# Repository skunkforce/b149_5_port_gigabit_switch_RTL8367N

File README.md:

# edgy_board number b149
This design is part of the [edgy board project](https://github.com/skunkforce/edgy_boards). It provides the functionality of chip XXXX via interfaces YYYY. 

# getting started
This repository uses submodules. After cloning use the command 

```$ git submodule update --init --recursive```

to pull the submodules before opening the project with kicad. 

# Tests
Tests can be found in [TESTS.md](TESTS.md)

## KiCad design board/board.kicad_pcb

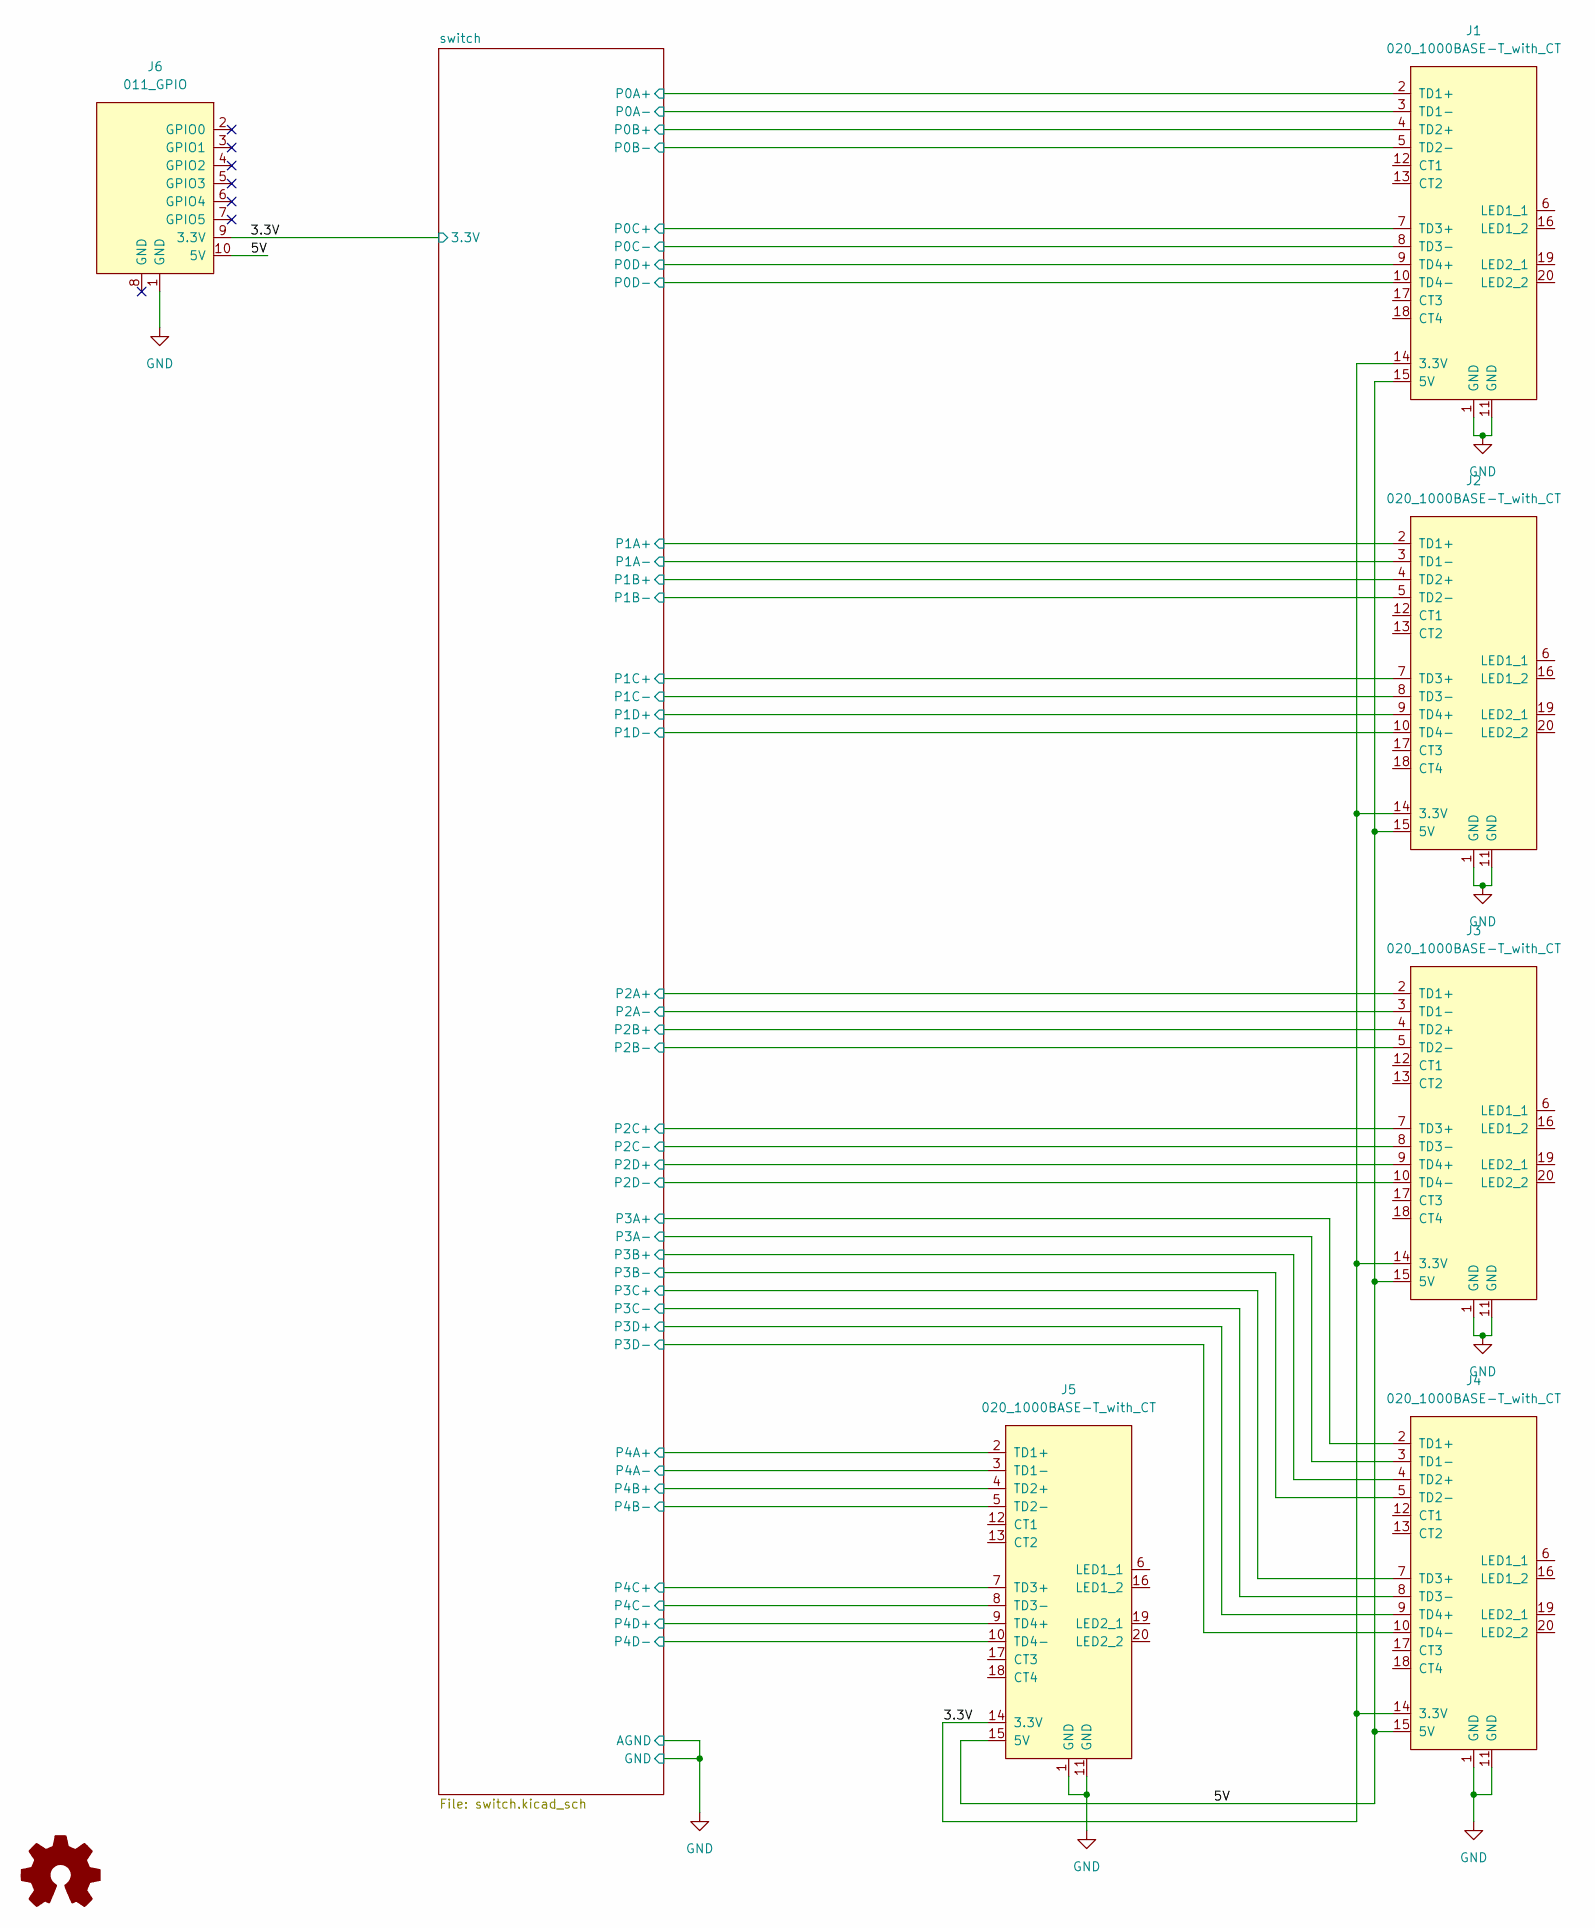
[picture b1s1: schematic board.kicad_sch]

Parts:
J1, J2, J3, J4, J5: 020_1000BASE-T_with_CT; on_edge_2x10_host
J6: 011_GPIO; on_edge_2x05_device
LOGO1: Logo_Open_Hardware_Small; OSHW-Symbol_6.7x6mm_SilkScreen

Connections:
/3.3V: J1.14 (3.3V), J2.14 (3.3V), J3.14 (3.3V), J4.14 (3.3V), J5.14 (3.3V), J6.9 (3.3V); also elsewhere on the board
/5V: J1.15 (5V), J2.15 (5V), J3.15 (5V), J4.15 (5V), J5.15 (5V), J6.10 (5V)
/switch/P0A+: J1.2 (TD1+); also elsewhere on the board
/switch/P0A-: J1.3 (TD1-); also elsewhere on the board
/switch/P0B+: J1.4 (TD2+); also elsewhere on the board
/switch/P0B-: J1.5 (TD2-); also elsewhere on the board
/switch/P0C+: J1.7 (TD3+); also elsewhere on the board
/switch/P0C-: J1.8 (TD3-); also elsewhere on the board
/switch/P0D+: J1.9 (TD4+); also elsewhere on the board
/switch/P0D-: J1.10 (TD4-); also elsewhere on the board
/switch/P1A+: J2.2 (TD1+); also elsewhere on the board
/switch/P1A-: J2.3 (TD1-); also elsewhere on the board
/switch/P1B+: J2.4 (TD2+); also elsewhere on the board
/switch/P1B-: J2.5 (TD2-); also elsewhere on the board
/switch/P1C+: J2.7 (TD3+); also elsewhere on the board
/switch/P1C-: J2.8 (TD3-); also elsewhere on the board
/switch/P1D+: J2.9 (TD4+); also elsewhere on the board
/switch/P1D-: J2.10 (TD4-); also elsewhere on the board
/switch/P2A+: J3.2 (TD1+); also elsewhere on the board
/switch/P2A-: J3.3 (TD1-); also elsewhere on the board
/switch/P2B+: J3.4 (TD2+); also elsewhere on the board
/switch/P2B-: J3.5 (TD2-); also elsewhere on the board
/switch/P2C+: J3.7 (TD3+); also elsewhere on the board
/switch/P2C-: J3.8 (TD3-); also elsewhere on the board
/switch/P2D+: J3.9 (TD4+); also elsewhere on the board
/switch/P2D-: J3.10 (TD4-); also elsewhere on the board
/switch/P3A+: J4.2 (TD1+); also elsewhere on the board
/switch/P3A-: J4.3 (TD1-); also elsewhere on the board
/switch/P3B+: J4.4 (TD2+); also elsewhere on the board
/switch/P3B-: J4.5 (TD2-); also elsewhere on the board
/switch/P3C+: J4.7 (TD3+); also elsewhere on the board
/switch/P3C-: J4.8 (TD3-); also elsewhere on the board
/switch/P3D+: J4.9 (TD4+); also elsewhere on the board
/switch/P3D-: J4.10 (TD4-); also elsewhere on the board
/switch/P4A+: J5.2 (TD1+); also elsewhere on the board
/switch/P4A-: J5.3 (TD1-); also elsewhere on the board
/switch/P4B+: J5.4 (TD2+); also elsewhere on the board
/switch/P4B-: J5.5 (TD2-); also elsewhere on the board
/switch/P4C+: J5.7 (TD3+); also elsewhere on the board
/switch/P4C-: J5.8 (TD3-); also elsewhere on the board
/switch/P4D+: J5.9 (TD4+); also elsewhere on the board
/switch/P4D-: J5.10 (TD4-); also elsewhere on the board
GND: J1.1 (GND), J1.11 (GND), J2.1 (GND), J2.11 (GND), J3.1 (GND), J3.11 (GND), J4.1 (GND), J4.11 (GND), J5.1 (GND), J5.11 (GND), J6.1 (GND); also elsewhere on the board

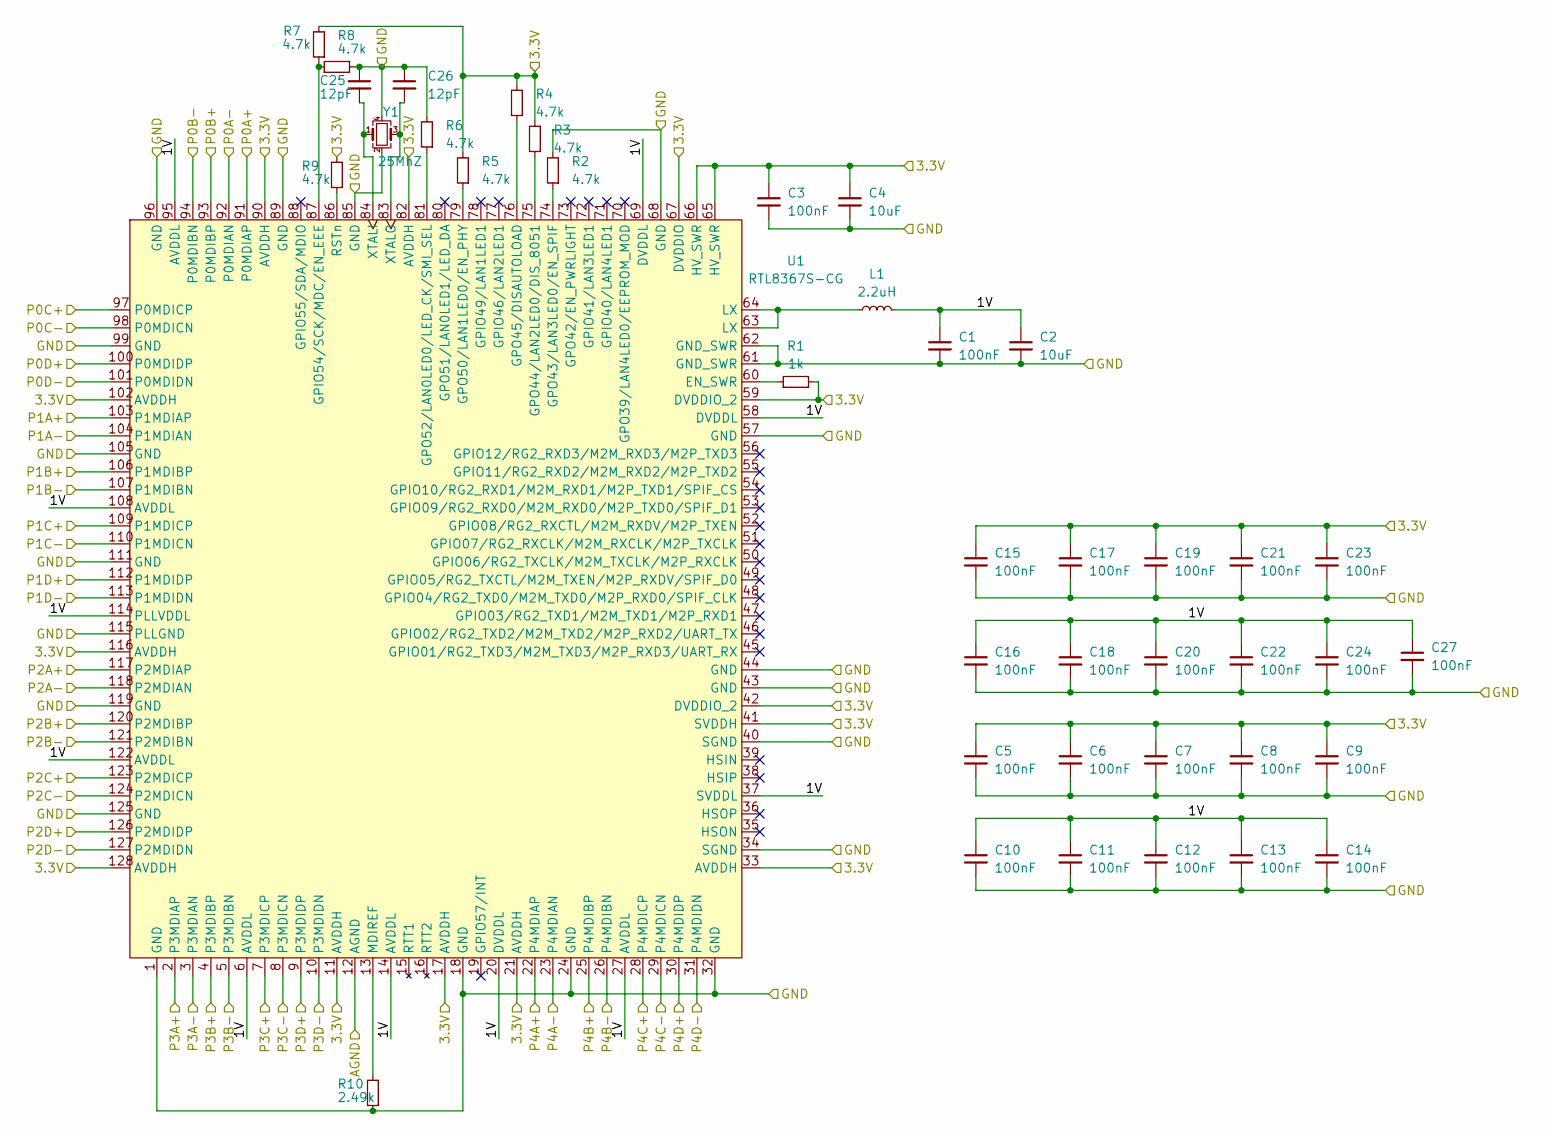
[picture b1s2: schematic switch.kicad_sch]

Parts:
C1, C3, C5, C6, C7, C8, C9, C10, C11, C12, C13, C14, C15, C16, C17, C18, C19, C20, C21, C22, C23, C24, C27: 100nF; C_0402_1005Metric; lcsc C1525
C2, C4: 10uF; C_0603_1608Metric; lcsc C19702
C25, C26: 12pF; C_0402_1005Metric; lcsc C1547
L1: 2.2uH; L_Sunlord_MWSA0402S; lcsc C408335
R1: 1k; R_0402_1005Metric; lcsc C11702
R2, R3, R4, R5, R6, R7, R8, R9: 4.7k; R_0402_1005Metric; lcsc C25900
R10: 2.49k; R_0402_1005Metric; lcsc C25884
U1: RTL8367S-CG; LQFP-128_14x14mm_P0.4mm; lcsc C2760849
Y1: 25MhZ; Crystal_SMD_3225-4Pin_3.2x2.5mm; lcsc C9006

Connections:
/3.3V: C3.1, C4.1, C5.1, C6.1, C7.1, C8.1, C9.1, C15.1, C17.1, C19.1, C21.1, C23.1, R1.2, R3.2, R4.2, R5.2, R8.2, R9.2, U1.11 (AVDDH), U1.17 (AVDDH), U1.21 (AVDDH), U1.33 (AVDDH), U1.41 (SVDDH), U1.42 (DVDDIO_2), U1.59 (DVDDIO_2), U1.65 (HV_SWR), U1.66 (HV_SWR), U1.67 (DVDDIO), U1.82 (AVDDH), U1.90 (AVDDH), U1.102 (AVDDH), U1.116 (AVDDH), U1.128 (AVDDH); also elsewhere on the board
/switch/1V: C1.1, C2.1, C10.1, C11.1, C12.1, C13.1, C14.1, C16.1, C18.1, C20.1, C22.1, C24.1, C27.1, L1.2, U1.6 (AVDDL), U1.14 (AVDDL), U1.20 (DVDDL), U1.27 (AVDDL), U1.37 (SVDDL), U1.58 (DVDDL), U1.69 (DVDDL), U1.95 (AVDDL), U1.108 (AVDDL), U1.114 (PLLVDDL), U1.122 (AVDDL)
/switch/P0A+: U1.91 (P0MDIAP); also elsewhere on the board
/switch/P0A-: U1.92 (P0MDIAN); also elsewhere on the board
/switch/P0B+: U1.93 (P0MDIBP); also elsewhere on the board
/switch/P0B-: U1.94 (P0MDIBN); also elsewhere on the board
/switch/P0C+: U1.97 (P0MDICP); also elsewhere on the board
/switch/P0C-: U1.98 (P0MDICN); also elsewhere on the board
/switch/P0D+: U1.100 (P0MDIDP); also elsewhere on the board
/switch/P0D-: U1.101 (P0MDIDN); also elsewhere on the board
/switch/P1A+: U1.103 (P1MDIAP); also elsewhere on the board
/switch/P1A-: U1.104 (P1MDIAN); also elsewhere on the board
/switch/P1B+: U1.106 (P1MDIBP); also elsewhere on the board
/switch/P1B-: U1.107 (P1MDIBN); also elsewhere on the board
/switch/P1C+: U1.109 (P1MDICP); also elsewhere on the board
/switch/P1C-: U1.110 (P1MDICN); also elsewhere on the board
/switch/P1D+: U1.112 (P1MDIDP); also elsewhere on the board
/switch/P1D-: U1.113 (P1MDIDN); also elsewhere on the board
/switch/P2A+: U1.117 (P2MDIAP); also elsewhere on the board
/switch/P2A-: U1.118 (P2MDIAN); also elsewhere on the board
/switch/P2B+: U1.120 (P2MDIBP); also elsewhere on the board
/switch/P2B-: U1.121 (P2MDIBN); also elsewhere on the board
/switch/P2C+: U1.123 (P2MDICP); also elsewhere on the board
/switch/P2C-: U1.124 (P2MDICN); also elsewhere on the board
/switch/P2D+: U1.126 (P2MDIDP); also elsewhere on the board
/switch/P2D-: U1.127 (P2MDIDN); also elsewhere on the board
/switch/P3A+: U1.2 (P3MDIAP); also elsewhere on the board
/switch/P3A-: U1.3 (P3MDIAN); also elsewhere on the board
/switch/P3B+: U1.4 (P3MDIBP); also elsewhere on the board
/switch/P3B-: U1.5 (P3MDIBN); also elsewhere on the board
/switch/P3C+: U1.7 (P3MDICP); also elsewhere on the board
/switch/P3C-: U1.8 (P3MDICN); also elsewhere on the board
/switch/P3D+: U1.9 (P3MDIDP); also elsewhere on the board
/switch/P3D-: U1.10 (P3MDIDN); also elsewhere on the board
/switch/P4A+: U1.22 (P4MDIAP); also elsewhere on the board
/switch/P4A-: U1.23 (P4MDIAN); also elsewhere on the board
/switch/P4B+: U1.25 (P4MDIBP); also elsewhere on the board
/switch/P4B-: U1.26 (P4MDIBN); also elsewhere on the board
/switch/P4C+: U1.28 (P4MDICP); also elsewhere on the board
/switch/P4C-: U1.29 (P4MDICN); also elsewhere on the board
/switch/P4D+: U1.30 (P4MDIDP); also elsewhere on the board
/switch/P4D-: U1.31 (P4MDIDN); also elsewhere on the board
GND: C1.2, C2.2, C3.2, C4.2, C5.2, C6.2, C7.2, C8.2, C9.2, C10.2, C11.2, C12.2, C13.2, C14.2, C15.2, C16.2, C17.2, C18.2, C19.2, C20.2, C21.2, C22.2, C23.2, C24.2, C25.1, C26.1, C27.2, R2.2, R6.2, R7.2, R10.1, U1.1 (GND), U1.12 (AGND), U1.18 (GND), U1.24 (GND), U1.32 (GND), U1.34 (SGND), U1.40 (SGND), U1.43 (GND), U1.44 (GND), U1.57 (GND), U1.61 (GND_SWR), U1.62 (GND_SWR), U1.68 (GND), U1.85 (GND), U1.89 (GND), U1.96 (GND), U1.99 (GND), U1.105 (GND), U1.111 (GND), U1.115 (PLLGND), U1.119 (GND), U1.125 (GND), Y1.2, Y1.4; also elsewhere on the board
unnamed: L1.1, U1.63 (LX), U1.64 (LX)
unnamed: R1.1, U1.60 (EN_SWR)
unnamed: R7.1, R8.1, U1.87 (GPIO54/SCK/MDC/EN_EEE)
unnamed: R2.1, U1.74 (GPO43/LAN3LED0/EN_SPIF)
unnamed: R3.1, U1.75 (GPO44/LAN2LED0/DIS_8051)
unnamed: R4.1, U1.76 (GPO45/DISAUTOLOAD)
unnamed: R5.1, U1.79 (GPO50/LAN1LED0/EN_PHY)
unnamed: R6.1, U1.81 (GPO52/LAN0LED0/LED_CK/SMI_SEL)
unnamed: R10.2, U1.13 (MDIREF)
unnamed: R9.1, U1.86 (RSTn)
unnamed: C25.2, U1.84 (XTALI), Y1.1
unnamed: C26.2, U1.83 (XTALO), Y1.3

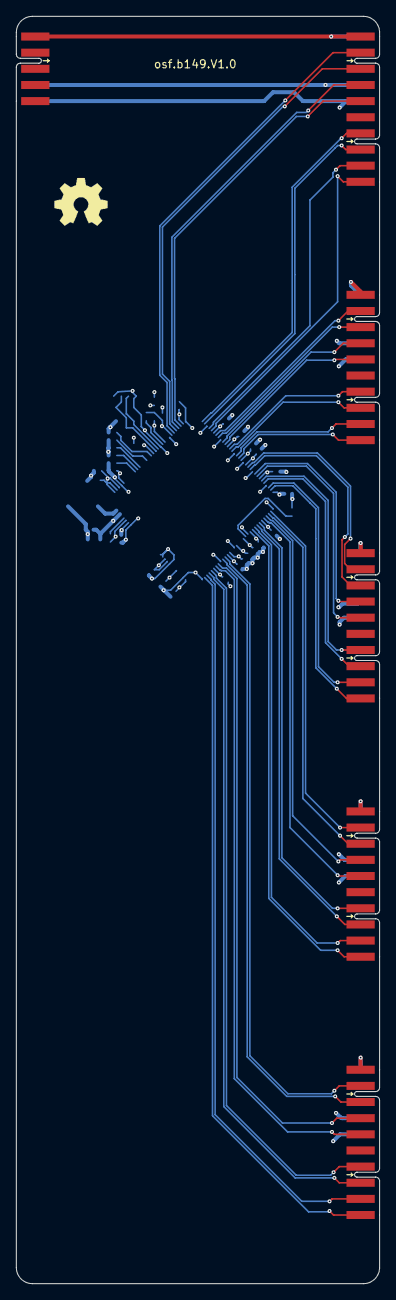
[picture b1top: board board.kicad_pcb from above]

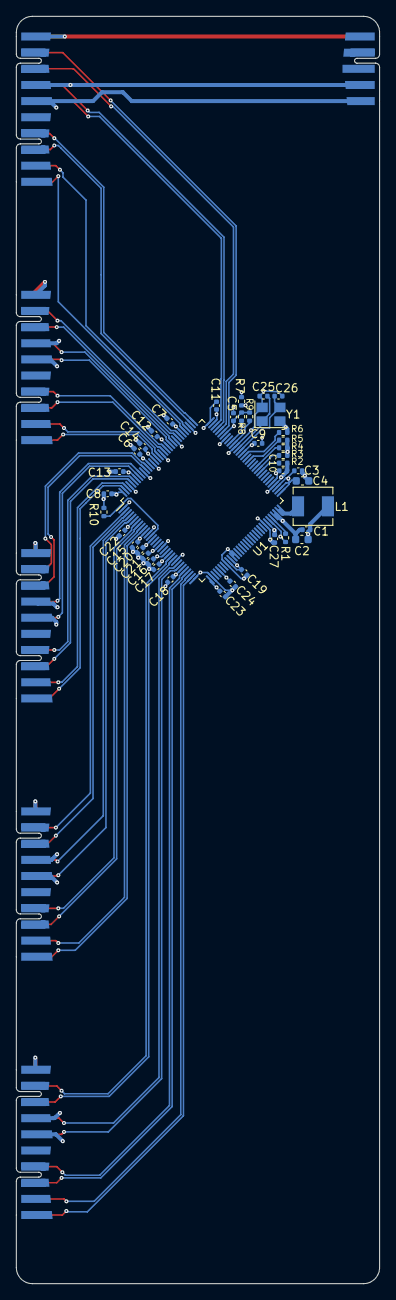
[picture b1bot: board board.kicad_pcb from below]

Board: 4 copper layers, 45.0 x 157.0 mm, 47 parts (40 on the bottom side), 56 nets.

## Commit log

2024-01-14 initial b149
2024-02-04 added lcsc part numbers
